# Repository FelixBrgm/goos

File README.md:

# We are currently fixing an issues please do not use the pcb files thx!
# Meet Goos, a minimalistic keyboard

A keyboard inspired by and base on [rae-dux](https://github.com/andrewjrae/rae-dux) with minimalistic black and white asthetic and a wonderfull "goos" designed by [Patrick <3](https://www.github.com/pgorner)

## Features
1. Minimal design - no diodes, LEDs, OLEDs
2. Ultra low-profile and transportable
3. Bluetooth
4. Battery powered
5. Mouting holes (some gerber files with some without)
7. A goos!

### Keymap
If you want to change the keymap, just fork this repo and open it with [Keymap Editor](https://nickcoutsos.github.io/keymap-editor/)

`Colemak-DH layer toggled by hitting the combo left-top && left-bottom keys`

`Symbol layer activated by holding down the right-middle thumb key`

`Numbers/Nav layer activated by holding down the left-middle thumb key`

`Macro layer activated by holding down both middle thumb keys`

`Game layer toggled by hitting the combo right-top && right-bottom keys`

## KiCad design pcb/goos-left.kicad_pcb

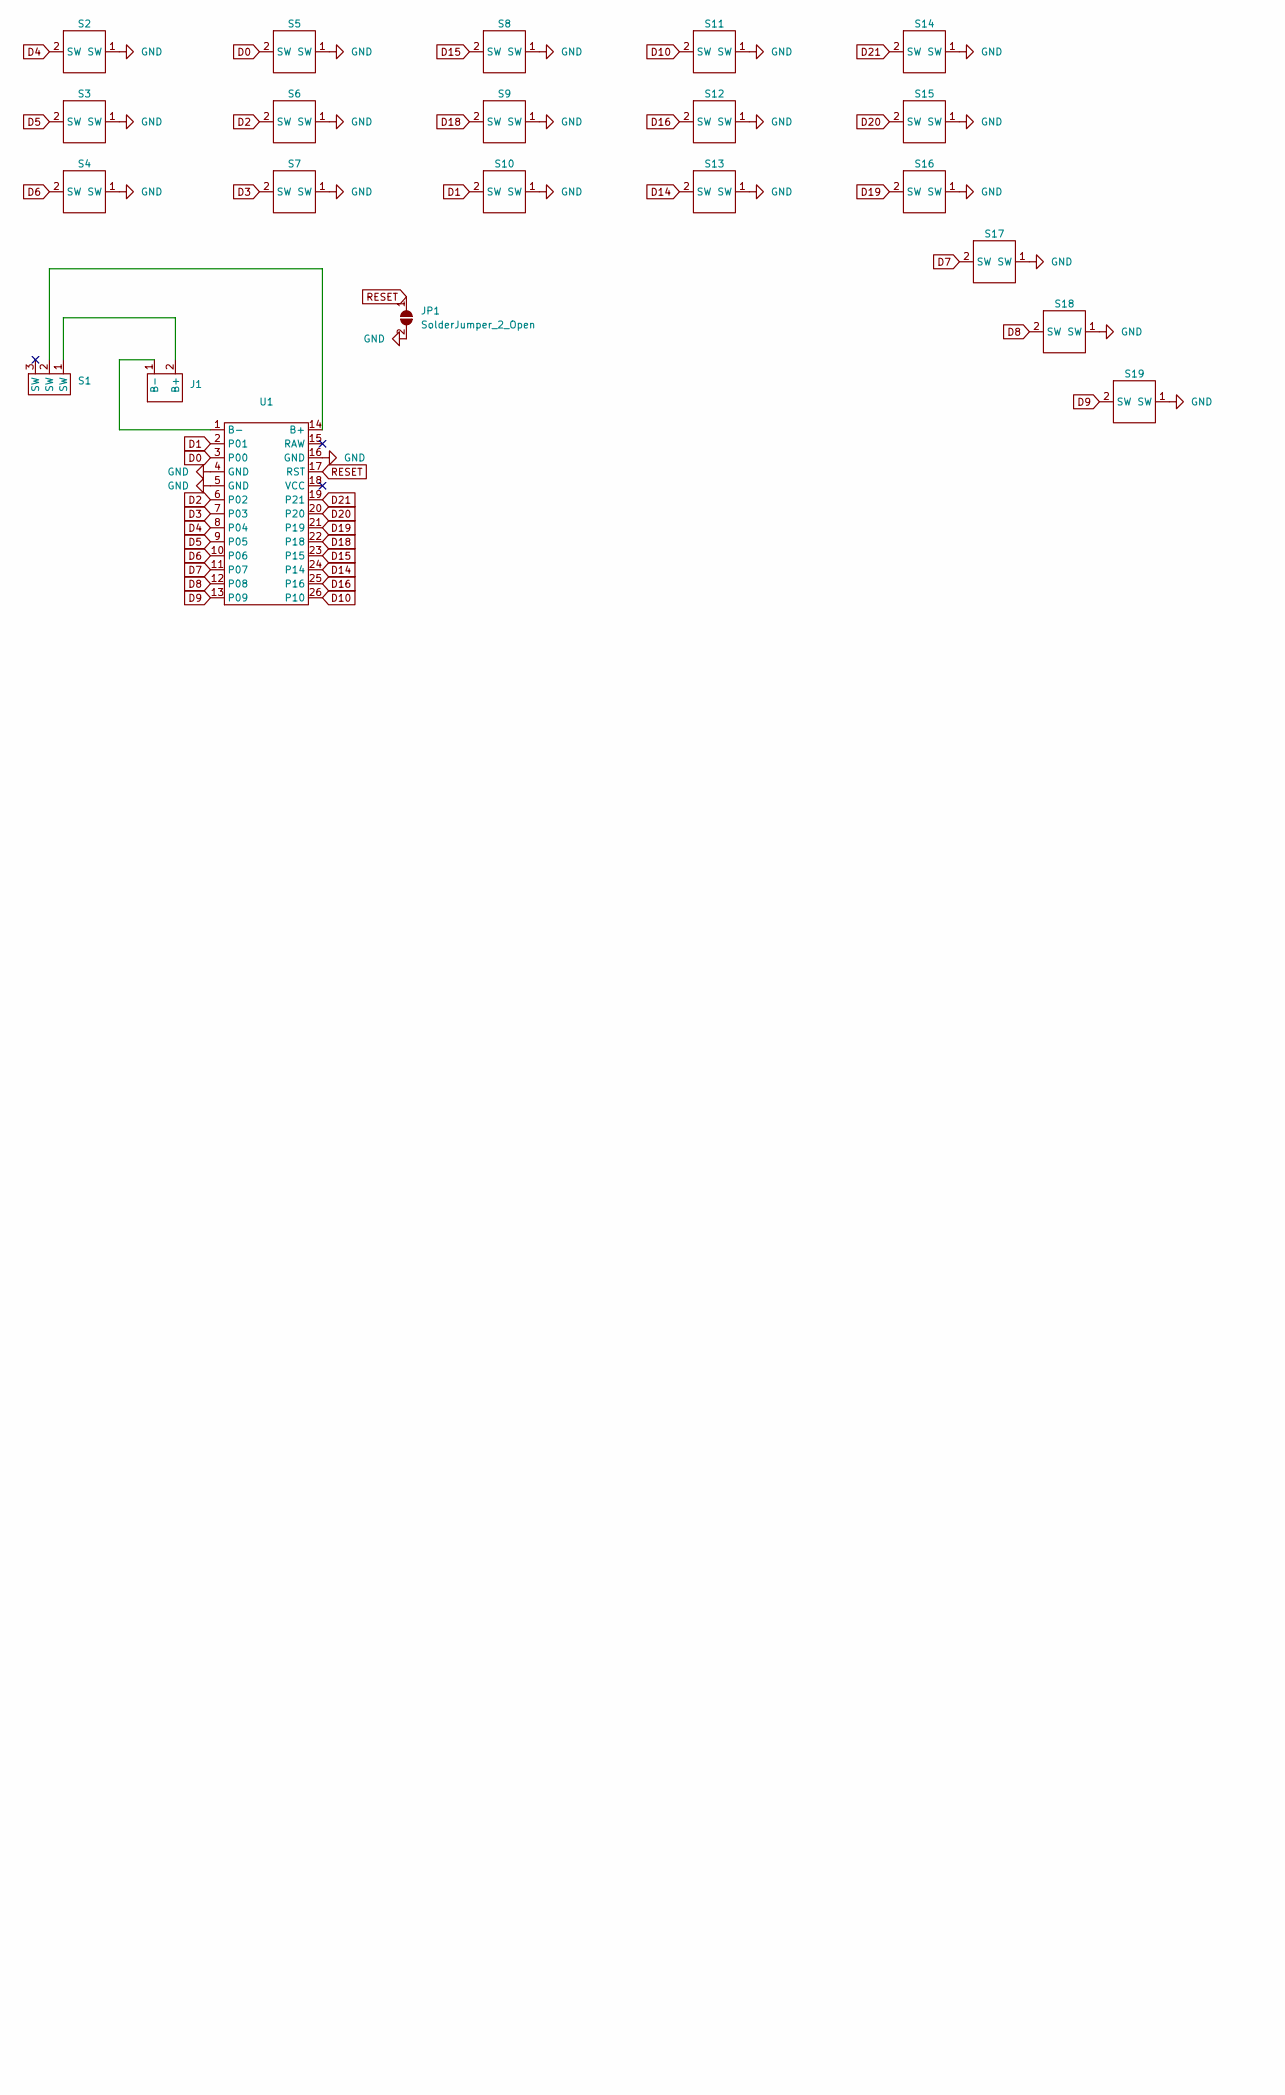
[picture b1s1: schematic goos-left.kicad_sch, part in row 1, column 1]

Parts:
J1: bat-connector
JP1: SolderJumper_2_Open; SolderJumper-2_P1.3mm_Open_TrianglePad1.0x1.5mm
S1: power-switch
S2, S3, S4, S5, S6, S7, S8, S9, S10, S11, S12, S13, S14, S15, S16, S17, S18, S19: switch-socket-kailh
U1: ProMicro

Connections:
D0: S5.2 (SW), U1.3 (P00)
D1: S10.2 (SW), U1.2 (P01)
D2: S6.2 (SW), U1.6 (P02)
D3: S7.2 (SW), U1.7 (P03)
D4: S2.2 (SW), U1.8 (P04)
D5: S3.2 (SW), U1.9 (P05)
D6: S4.2 (SW), U1.10 (P06)
D7: S17.2 (SW), U1.11 (P07)
D8: S18.2 (SW), U1.12 (P08)
D9: S19.2 (SW), U1.13 (P09)
D10: S11.2 (SW), U1.26 (P10)
D14: S13.2 (SW), U1.24 (P14)
D15: S8.2 (SW), U1.23 (P15)
D16: S12.2 (SW), U1.25 (P16)
D18: S9.2 (SW), U1.22 (P18)
D19: S16.2 (SW), U1.21 (P19)
D20: S15.2 (SW), U1.20
D21: S14.2 (SW), U1.19 (P21)
GND: JP1.2 (B), S2.1 (SW), S3.1 (SW), S4.1 (SW), S5.1 (SW), S6.1 (SW), S7.1 (SW), S8.1 (SW), S9.1 (SW), S10.1 (SW), S11.1 (SW), S12.1 (SW), S13.1 (SW), S14.1 (SW), S15.1 (SW), S16.1 (SW), S17.1 (SW), S18.1 (SW), S19.1 (SW), U1.4 (GND), U1.5 (GND), U1.16 (GND); also elsewhere on the board
unnamed: J1.2 (B+), S1.1 (SW)
unnamed: J1.1 (B-), U1.1 (B-)
unnamed: S1.2 (SW), U1.14 (B+)
RESET: JP1.1 (A), U1.17 (RST); also elsewhere on the board

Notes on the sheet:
Marvin

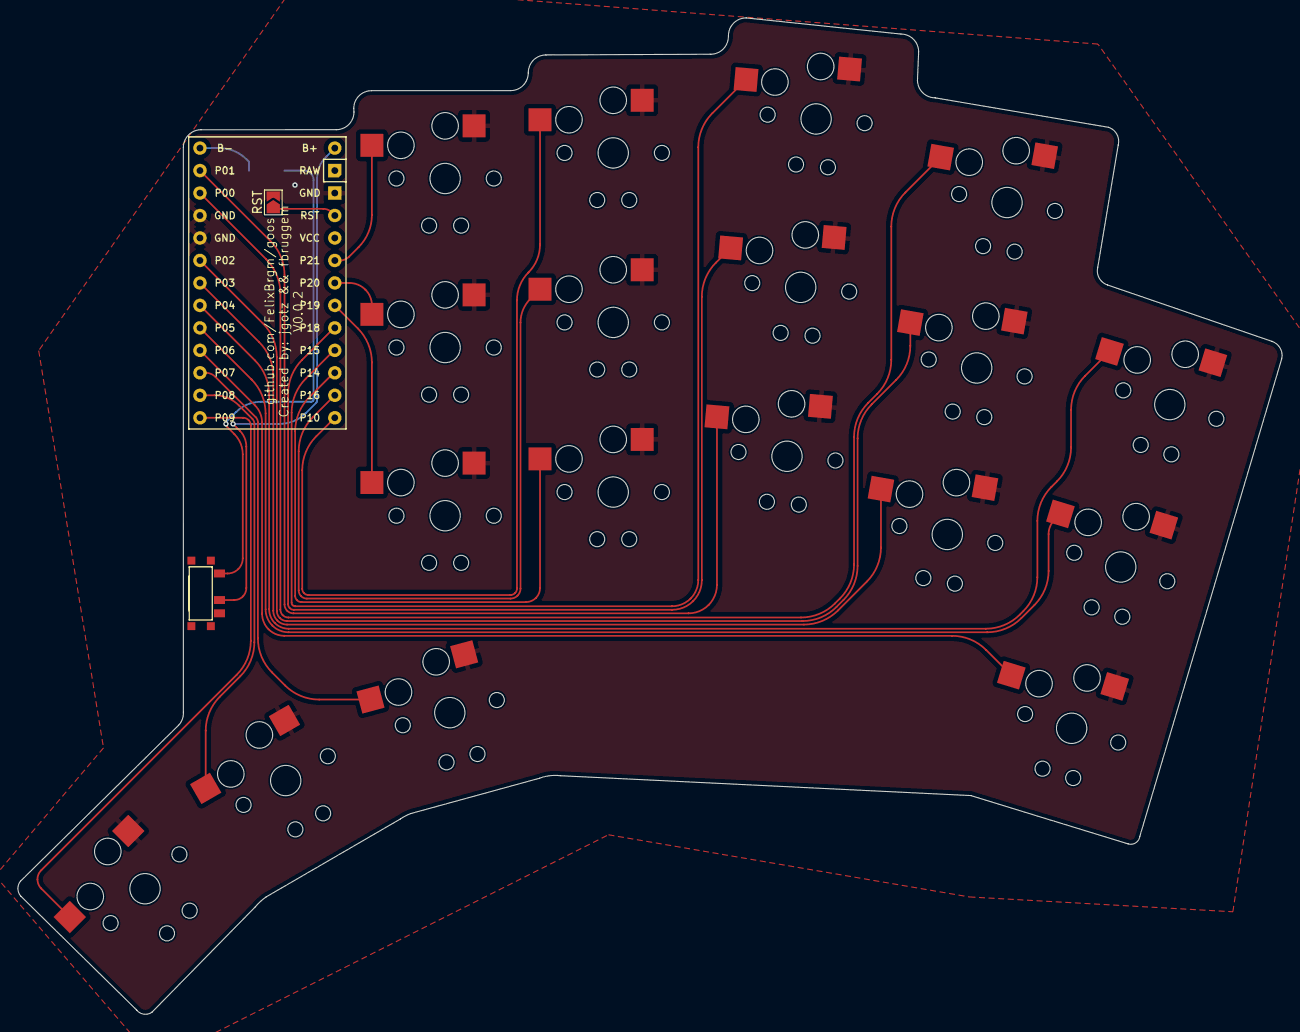
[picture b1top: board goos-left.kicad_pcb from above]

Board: 2 copper layers, 142.9 x 112.6 mm, 22 parts (1 on the bottom side), 23 nets.

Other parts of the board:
RST: SolderJumper_2_Open; SolderJumper-2_P1.3mm_Open_TrianglePad1.0x1.5mm

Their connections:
GND: RST.2 (B); also elsewhere on the board
RESET: RST.1 (A); also elsewhere on the board

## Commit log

2024-03-24 Init
2024-03-24 Added workflow
2024-03-24 Changed Keyboard name
2024-03-24 Custom Keymap made
2024-03-24 Fixed layout typo
2024-03-24 Another typo fix
2024-03-24 Last typo?
2024-03-24 Last one!
2024-03-24 NOW!
2024-03-24 ahhhhhh!
2024-03-24 why_why_why
2024-03-24 Updated rae_dux.keymap
2024-03-25 Added tri layer
2024-03-25 fixed
2024-03-25 added macro
2024-03-25 changed esc
2024-03-25 Changed home-row-mods to balanced
2024-03-26 Added bootloader
2024-03-26 new bootloader
2024-03-26 newer one
2024-03-26 new bootloader test
2024-03-26 removed settings layer
2024-03-26 fixed mute
2024-03-30 first arrangement
2024-03-30 rearanged because of button to activate layer
2024-04-03 changed number arrangement
2024-04-13 fix ctrl alt command shift
2024-06-08 Renamed
2024-06-08 Renamed Readme
2024-06-08 Added Layout images
2024-06-08 added description
2024-06-08 feat: left side done, started right
2024-06-08 added colemak-dh
2024-06-08 feat: right side routed
2024-06-08 Test out
2024-06-08 feat: right side rounded and filled
2024-06-08 fix: Unconnected ground planes
2024-06-08 fix: move silkscreen to backside
2024-06-08 fix: rename PCB folder
2024-06-08 feat: added github text
2024-06-08 feat: add gerbers
2024-06-08 fix: remove grbr
2024-06-22 fix: switch being permanently on
2024-11-13 Update DONT USE THESE RN THEY ARE OUTDATED BUT SHOULD BE FIXED IN THE NEXT DAYS
2024-11-13 Update DONT USE THESE FILES
2024-11-17 feat: fixed right half
2024-11-17 feat: updated gerbers
2024-11-30 fix: how is a unconnected ground plane not a DRC error
2024-11-30 fix: move pads further apart
2024-12-01 moved settings to different place
2025-03-05 Fixed v3 issues
2025-06-11 Updated goos.keymap
